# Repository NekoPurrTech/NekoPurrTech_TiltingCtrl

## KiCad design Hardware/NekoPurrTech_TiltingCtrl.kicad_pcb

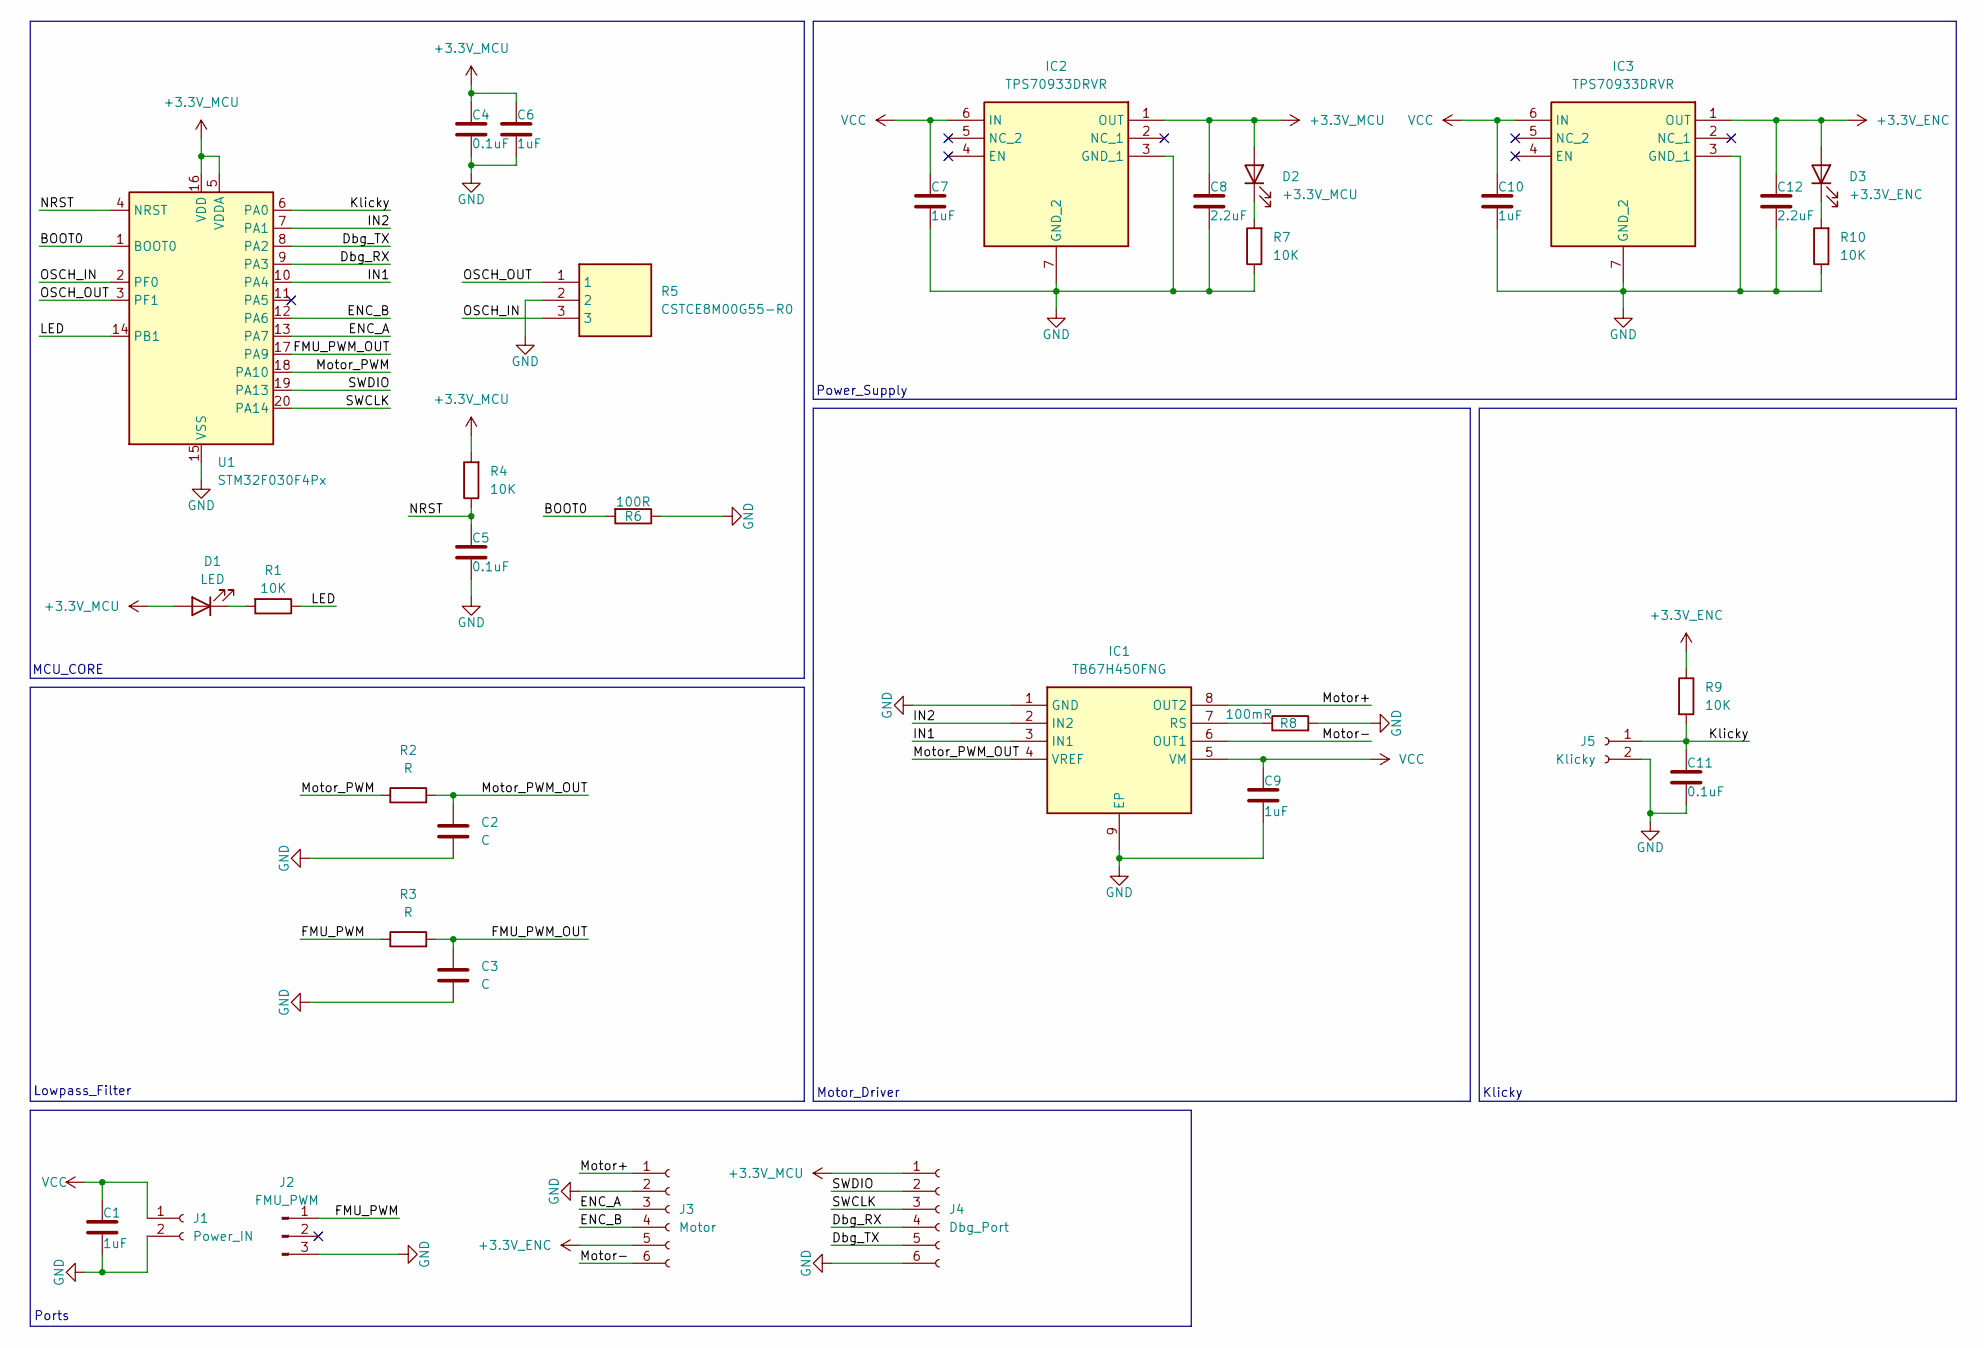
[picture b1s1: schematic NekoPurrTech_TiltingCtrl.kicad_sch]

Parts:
C1, C6, C7, C9, C10: 1uF; C_0603_1608Metric
C2, C3: C; C_0603_1608Metric
C4, C5, C11: 0.1uF; C_0603_1608Metric
C8, C12: 2.2uF; C_0603_1608Metric
D1: LED; LED_0603_1608Metric
D2: +3.3V_MCU; LED_0603_1608Metric
D3: +3.3V_ENC; LED_0603_1608Metric
IC1: TB67H450FNG; SOIC127P600X175-9N; Manufacturer_Part_Number TB67H450FNG; Mouser Part Number N/A
IC2, IC3: TPS70933DRVR; SON65P200X200X80-7N; Manufacturer_Part_Number TPS70933DRVR; Mouser Part Number 595-TPS70933DRVR
J1: Power_IN; PinHeader_1x02_P2.54mm_Vertical
J2: FMU_PWM; PinHeader_1x03_P2.54mm_Vertical
J3: Motor; PinHeader_1x06_P2.54mm_Vertical
J4: Dbg_Port; PinHeader_1x06_P2.54mm_Vertical
J5: Klicky; PinHeader_1x02_P2.54mm_Vertical
R1, R4, R7, R9, R10: 10K; R_0603_1608Metric
R2, R3: R; R_0603_1608Metric
R5: CSTCE8M00G55-R0; CSTCE12M0G55-R0; Manufacturer_Part_Number CSTCE8M00G55-R0; Mouser Part Number 81-CSTCE8M00G55-R0
R6: 100R; R_0603_1608Metric
R8: 100mR; R_1206_3216Metric
U1: STM32F030F4Px; TSSOP-20_4.4x6.5mm_P0.65mm

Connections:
+3.3V_ENC: C12.1, D3.2 (A), IC3.1 (OUT), J3.5, R9.1
+3.3V_MCU: C4.1, C6.1, C8.1, D1.2 (A), D2.2 (A), IC2.1 (OUT), J4.1, R4.2, U1.5 (VDDA), U1.16 (VDD)
/BOOT0: R6.2, U1.1 (BOOT0)
/Dbg_RX: J4.4, U1.9 (PA3)
/Dbg_TX: J4.5, U1.8 (PA2)
/ENC_A: J3.3, U1.13 (PA7)
/ENC_B: J3.4, U1.12 (PA6)
/FMU_PWM: J2.1, R3.1
/FMU_PWM_OUT: C3.1, R3.2, U1.17 (PA9)
/IN1: IC1.3 (IN1), U1.10 (PA4)
/IN2: IC1.2 (IN2), U1.7 (PA1)
/Klicky: C11.1, J5.1, R9.2, U1.6 (PA0)
/LED: R1.1, U1.14 (PB1)
/Motor+: IC1.8 (OUT2), J3.1
/Motor-: IC1.6 (OUT1), J3.6
/Motor_PWM: R2.1, U1.18 (PA10)
/Motor_PWM_OUT: C2.1, IC1.4 (VREF), R2.2
/NRST: C5.1, R4.1, U1.4 (NRST)
/OSCH_IN: R5.3, U1.2 (PF0)
/OSCH_OUT: R5.1, U1.3 (PF1)
/SWCLK: J4.3, U1.20 (PA14)
/SWDIO: J4.2, U1.19 (PA13)
GND: C1.2, C2.2, C3.2, C4.2, C5.2, C6.2, C7.2, C8.2, C9.2, C10.2, C11.2, C12.2, IC1.1 (GND), IC1.9 (EP), IC2.3 (GND_1), IC2.7 (GND_2), IC3.3 (GND_1), IC3.7 (GND_2), J1.2, J2.3, J3.2, J4.6, J5.2, R5.2, R6.1, R7.1, R8.2, R10.1, U1.15 (VSS)
unnamed: D1.1 (K), R1.2
unnamed: D2.1 (K), R7.2
unnamed: D3.1 (K), R10.2
unnamed: IC1.7 (RS), R8.1
VCC: C1.1, C7.1, C9.1, C10.1, IC1.5 (VM), IC2.6 (IN), IC3.6 (IN), J1.1

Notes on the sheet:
Klicky
MCU_CORE
Lowpass_Filter
Motor_Driver
Ports
Power_Supply

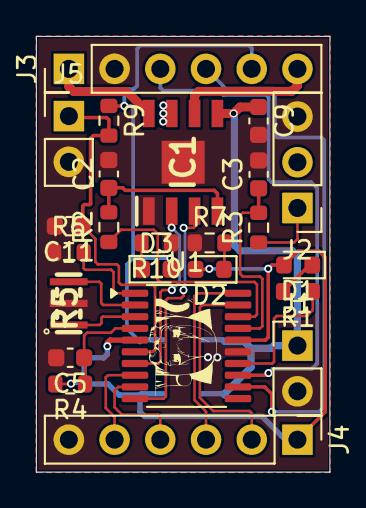
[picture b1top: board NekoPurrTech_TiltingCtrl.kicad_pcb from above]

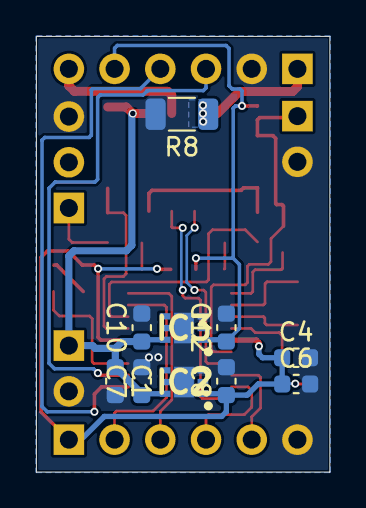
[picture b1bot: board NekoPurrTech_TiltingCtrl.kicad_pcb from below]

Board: 2 copper layers, 16.3 x 24.2 mm, 34 parts (10 on the bottom side), 28 nets.

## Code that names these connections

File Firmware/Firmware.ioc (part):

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Mcu.Name=STM32F030F4Px
Mcu.Package=TSSOP20
Mcu.UserName=STM32F030F4Px
PA0.GPIOParameters=GPIO_Label
PA0.GPIO_Label=Klicky
PA0.Signal=GPIO_Input
PA10.Signal=S_TIM1_CH3
PA13.Mode=Serial_Wire
PA13.Signal=SYS_SWDIO
PA14.Mode=Serial_Wire
PA14.Signal=SYS_SWCLK
PA2.Mode=Asynchronous
PA2.Signal=USART1_TX
PA3.Mode=Asynchronous
PA3.Signal=USART1_RX
PA4.GPIOParameters=GPIO_Label
PA4.GPIO_Label=IN1
PA4.Signal=GPIO_Output
PA5.GPIOParameters=GPIO_Label
PA5.GPIO_Label=IN2
PA5.Signal=GPIO_Output
PA6.Signal=S_TIM3_CH1
PA7.Signal=S_TIM3_CH2
PA9.Signal=S_TIM1_CH2
PB1.GPIOParameters=PinState,GPIO_Label
PB1.GPIO_Label=LED
PB1.PinState=GPIO_PIN_SET
PB1.Signal=GPIO_Output
PF0-OSC_IN.Mode=HSE-External-Oscillator
PF0-OSC_IN.Signal=RCC_OSC_IN
PF1-OSC_OUT.Mode=HSE-External-Oscillator
PF1-OSC_OUT.Signal=RCC_OSC_OUT
RCC.SYSCLKFreq_VALUE=48000000
RCC.SYSCLKSource=RCC_SYSCLKSOURCE_PLLCLK
board=custom

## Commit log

2025-02-23 Finished Project
